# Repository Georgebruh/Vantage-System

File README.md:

# Vantage

Design files and firmware of the **Vantage** IoT sensor node, by Team sevenUP. The node is the field unit of a
flood-monitoring system. This repository holds the hardware (schematics, PCB layout, libraries, drawings and the
instruction documents) and the node firmware.

**Current revision: Rev A** (2026-10-25), tag `rev-A`.

| Board | Status |
|---|---|
| Sensor board | Schematic and PCB complete. Single-sided, made at home by toner transfer. |
| Power board | Schematic complete. PCB layout not started yet. |

The node is two boards joined by one 6-way JST XH cable (J1 to J1):

- **Sensor board**: carries the ESP32-S3 dev board (YD-ESP32-S3, header rows 25.4 mm apart) and the sensor
  interfaces: AJ-SR04M ultrasonic, BME280, rain gauge, TF-Luna (optional).
- **Power board**: 18650 cell with protection, solar MPPT charger, 3.3 V buck-boost with ideal diode, switched
  5 V for the sensors (SENS_EN) and two INA226 current monitors.

## Repository layout

```
Vantage-Hardware/
├── sensor-board/           KiCad project of the sensor board (schematic + PCB)
├── power-board/            KiCad project of the power board (schematic)
├── lib/                    shared Vantage symbol and footprint library
├── outputs/
│   ├── sensor-board/       schematic PDF, copper artwork, assembly drawing, BOM, drill table
│   └── power-board/        schematic PDF, BOM
├── docs/                   instruction documents (PDF)
│   └── src/                document sources, figures, fonts and build script
├── firmware/               ESP32-S3 firmware (PlatformIO) and the gateway receiver
└── tools/                  script that regenerates the drawings in outputs/
```

## Files

### KiCad design files

| File | Description |
|---|---|
| `sensor-board/Vantage_Sensor.kicad_pro` | Sensor board project (design rules for toner transfer: 0.6 / 1.0 mm tracks, 0.5 mm gaps) |
| `sensor-board/Vantage_Sensor.kicad_sch` | Sensor board schematic |
| `sensor-board/Vantage_Sensor.kicad_pcb` | Sensor board PCB, 110 × 30 mm, copper on the bottom only, two wire links on top |
| `sensor-board/fp-lib-table`, `sym-lib-table` | Project library tables, pointing to `lib/` |
| `power-board/Vantage_Power.kicad_pro` | Power board project (same toner-transfer design rules, ready for the layout) |
| `power-board/Vantage_Power.kicad_sch` | Power board schematic |
| `power-board/fp-lib-table`, `sym-lib-table` | Project library tables, pointing to `lib/` |

### Library

| File | Description |
|---|---|
| `lib/Vantage.kicad_sym` | Symbols: ESP32-S3 dev board, INA226 module, CN3791, BMS and DC-DC modules, LM66100, TPS2051B |
| `lib/Vantage.pretty/` | Footprints with enlarged pads for toner transfer and hand drilling; SMD footprints placed on the copper side |

### Drawings and tables (`outputs/`)

| File | Description |
|---|---|
| `outputs/sensor-board/Vantage_Sensor_Schematic.pdf` | Sensor board schematic |
| `outputs/sensor-board/Vantage_Sensor_Copper-Artwork_Letter.pdf` | Copper artwork, 1:1, four copies on US Letter. **Print at 100 % / Actual size, do not mirror.** |
| `outputs/sensor-board/Vantage_Sensor_Copper-Artwork_A4.pdf` | Same, on A4 |
| `outputs/sensor-board/Vantage_Sensor_Assembly-Drawing.pdf` | Assembly drawing, 2:1: component side and copper side |
| `outputs/sensor-board/Vantage_Sensor_BOM.csv` | Sensor board bill of materials |
| `outputs/sensor-board/Vantage_Sensor_Drill.csv` | Drill sizes and counts |
| `outputs/power-board/Vantage_Power_Schematic.pdf` | Power board schematic |
| `outputs/power-board/Vantage_Power_BOM.csv` | Power board bill of materials |

### Documents (`docs/`)

The documents follow the layout of ISO documents: cover, contents, foreword, introduction, numbered clauses
(scope, references, terms, ...), normative and informative annexes, bibliography.

| File | Description |
|---|---|
| `docs/VNT-001_Sensor-board_Fabrication-assembly-test.pdf` | **VNT-001** Vantage — Sensor board — Fabrication, assembly and test |
| `docs/VNT-002_Power-board_Description-and-test.pdf` | **VNT-002** Vantage — Power board — Description and test |
| `docs/src/VNT-001.md`, `VNT-002.md` | Document sources (edit these, then rebuild the PDFs) |
| `docs/src/build.py` | Builds the PDFs from the sources |
| `docs/src/iso.css` | Page layout and styles |
| `docs/src/figures/` | Figures used by the documents |
| `docs/src/fonts/` | Caladea font (SIL Open Font License, `OFL.txt`) |

### Firmware (`firmware/`)

| File | Description |
|---|---|
| `firmware/README.md` | Setup, build environments, power modes and the data format |
| `firmware/platformio.ini` | PlatformIO project: `field` (normal operation) and `bench` (bench and functional tests) |
| `firmware/include/config.h` | Node ID, gateway URL, mounting height, intervals and battery thresholds |
| `firmware/include/pins.h` | Pin map (VNT-001, Annex C) |
| `firmware/include/secrets.example.h` | Template for the Wi-Fi credentials; copy to `secrets.h`, which is not committed |
| `firmware/src/` | Firmware sources: sensors, rain gauge, power monitors, uplink, sleep and power modes |
| `firmware/tools/receiver.py` | Receiver for the gateway computer; writes the readings to a CSV file |

### Tools

| File | Description |
|---|---|
| `tools/make_outputs.py` | Regenerates the schematic PDFs, copper artwork, assembly drawing and document figures with `kicad-cli` |

## Opening the design

The KiCad files are in the KiCad 7 format; KiCad 8, 9 and 10 open them. The first save in KiCad 10 upgrades the
file format; commit that upgrade on its own, without other changes, so later diffs stay readable.

Both projects use the shared library in `lib/` through their own library tables, so no global library setup is
needed.

## Title blocks

Every file carries the same title block content: **Team sevenUP**, title **Vantage — Sensor board** or
**Vantage — Power board**, date and revision. No comment lines. The documents carry the same fields in the title
block on their cover.

## Revisions

All files of a release share one revision letter, shown in every title block and on the document covers. Each
release is tagged `rev-<letter>` and listed in [`CHANGELOG.md`](CHANGELOG.md). Things that need to change are
tracked as GitHub issues.

To make a new revision:

1. Change the design in KiCad.
2. Set the new revision letter and date in the title block of every changed file (Page Settings in KiCad).
3. Regenerate the drawings: `python3 tools/make_outputs.py`, or plot them from KiCad.
4. Update the BOM and drill CSV files if parts or holes changed.
5. Update the document sources (`edition`, `date`, `rev` and the content) and rebuild: `python3 docs/src/build.py`.
6. Add the revision to `CHANGELOG.md`, commit, and tag it `rev-<letter>`.

## Rebuilding the outputs

Drawings (needs KiCad's `kicad-cli` on the PATH, or its path in `KICAD_CLI`):

```
pip install pypdf reportlab
python3 tools/make_outputs.py
```

Documents:

```
pip install markdown beautifulsoup4 weasyprint
python3 docs/src/build.py
```

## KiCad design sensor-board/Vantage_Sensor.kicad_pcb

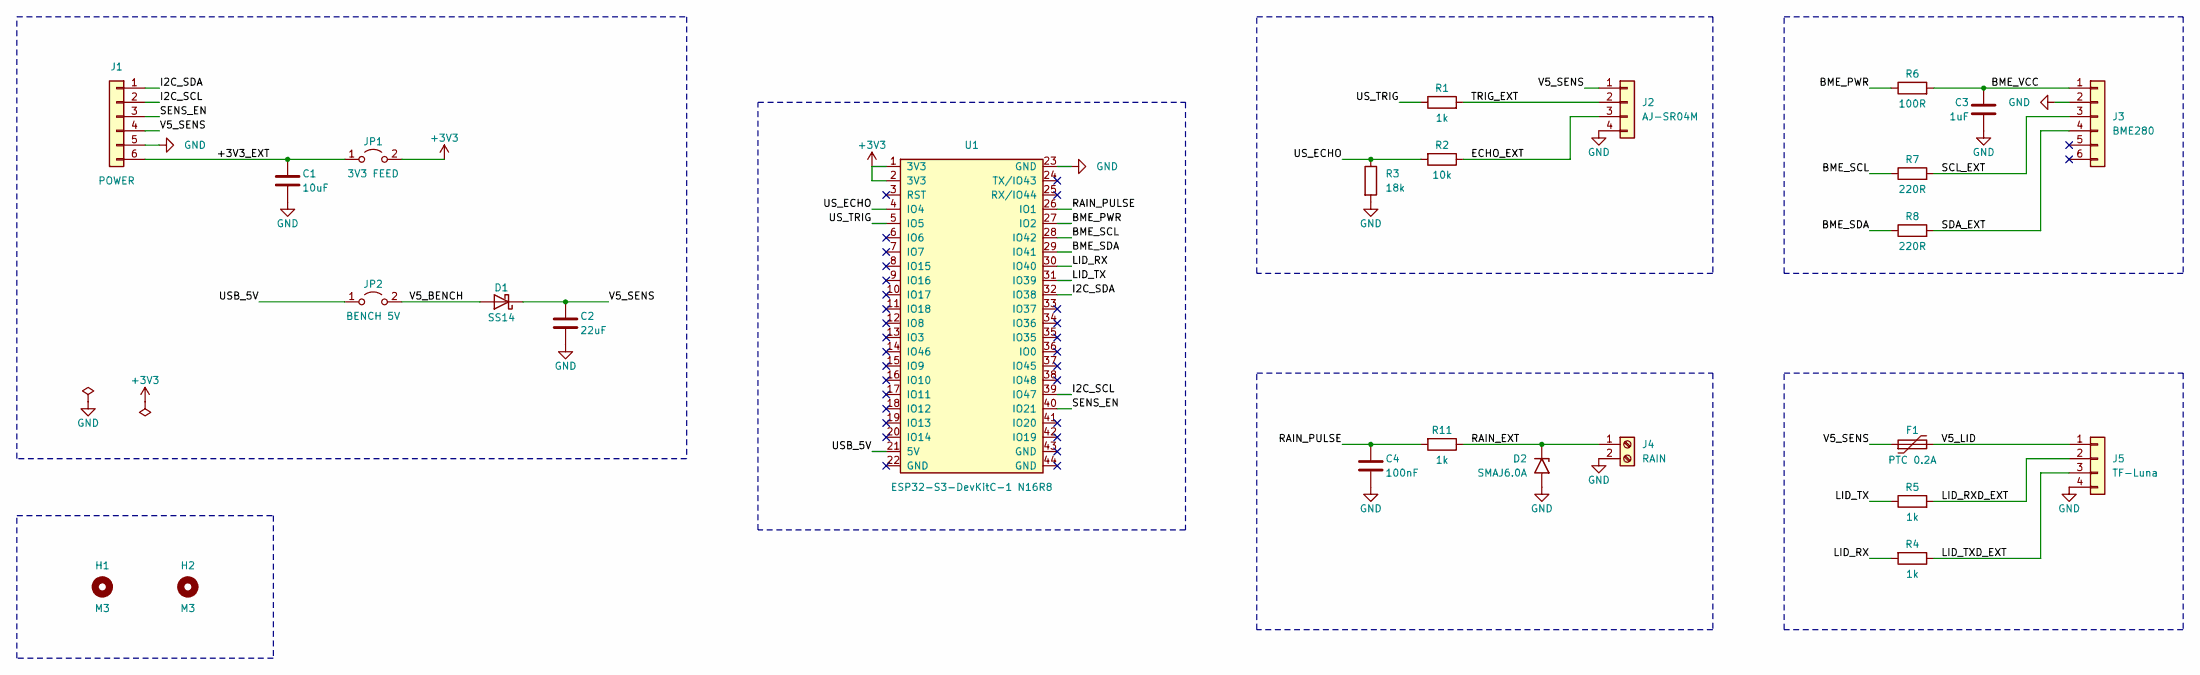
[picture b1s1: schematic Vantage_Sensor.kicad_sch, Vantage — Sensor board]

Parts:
C1: 10uF; C_1206_HandSolder_Bottom
C2: 22uF; C_1206_HandSolder_Bottom
C3: 1uF; C_1206_HandSolder_Bottom
C4: 100nF; C_1206_HandSolder_Bottom
D1: SS14; D_SMA_HandSolder_Bottom
D2: SMAJ6.0A; D_SMA_HandSolder_Bottom
F1: PTC 0.2A; Fuse_1812_HandSolder_Bottom
H1, H2: M3; MountingHole_3.2mm_M3_KeepCopper3.5mm
J1: POWER; JST_XH_S6B-XH-A_1x06_P2.50mm_Horizontal_Toner
J2: AJ-SR04M; AJ-SR04M_Socket_1x04_Upright
J3: BME280; PinSocket_1x06_P2.54mm_Vertical_Toner
J4: RAIN; TerminalBlock_3.5mm_1x02_Toner
J5: TF-Luna; PinHeader_1x04_P2.54mm_Vertical_Toner
JP1: 3V3 FEED; PinHeader_1x02_P2.54mm_Vertical_Toner
JP2: BENCH 5V; PinHeader_1x02_P2.54mm_Vertical_Toner
R1, R4, R5, R11: 1k; R_1206_HandSolder_Bottom
R2: 10k; R_1206_HandSolder_Bottom
R3: 18k; R_1206_HandSolder_Bottom
R6: 100R; R_1206_HandSolder_Bottom
R7, R8: 220R; R_1206_HandSolder_Bottom
U1: ESP32-S3-DevKitC-1 N16R8; ESP32-S3-DevKitC-1_Socket_Row25.40mm

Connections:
+3V3: JP1.2 (B), U1.1 (3V3), U1.2 (3V3)
/+3V3_EXT: C1.1, J1.6, JP1.1 (A)
/BME_PWR: R6.1, U1.27 (IO2)
/BME_SCL: R7.1, U1.28 (IO42)
/BME_SDA: R8.1, U1.29 (IO41)
/BME_VCC: C3.1, J3.1, R6.2
/ECHO_EXT: J2.3, R2.1
/I2C_SCL: J1.2, U1.39 (IO47)
/I2C_SDA: J1.1, U1.32 (IO38)
/LID_RX: R4.2, U1.30 (IO40)
/LID_RXD_EXT: J5.2, R5.2
/LID_TX: R5.1, U1.31 (IO39)
/LID_TXD_EXT: J5.3, R4.1
/RAIN_EXT: D2.1 (A1), J4.1, R11.1
/RAIN_PULSE: C4.1, R11.2, U1.26 (IO1)
/SCL_EXT: J3.3, R7.2
/SDA_EXT: J3.4, R8.2
/SENS_EN: J1.3, U1.40 (IO21)
/TRIG_EXT: J2.2, R1.2
/USB_5V: JP2.1 (A), U1.21 (5V)
/US_ECHO: R2.2, R3.1, U1.4 (IO4)
/US_TRIG: R1.1, U1.5 (IO5)
/V5_BENCH: D1.2 (A), JP2.2 (B)
/V5_LID: F1.2, J5.1
/V5_SENS: C2.1, D1.1 (K), F1.1, J1.4, J2.1
GND: C1.2, C2.2, C3.2, C4.2, D2.2 (A2), J1.5, J2.4, J3.2, J4.2, J5.4, R3.2, U1.23 (GND)

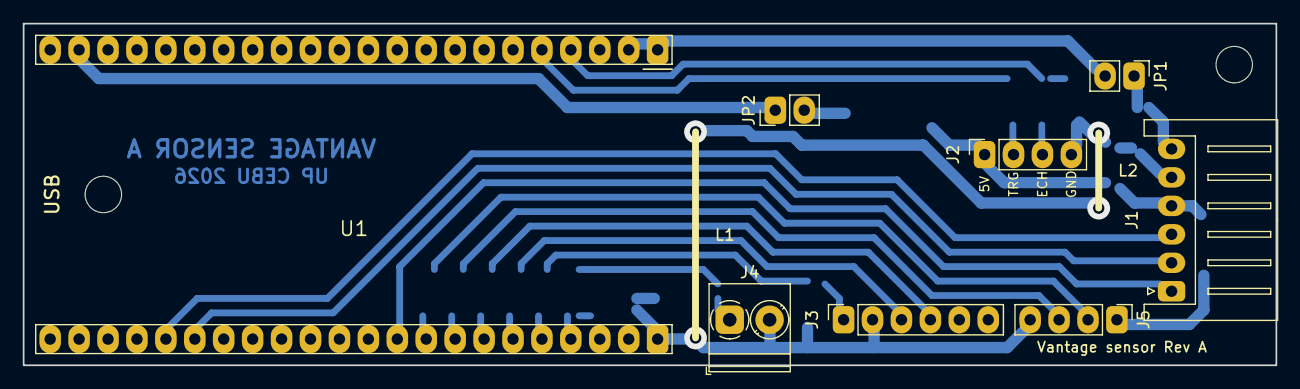
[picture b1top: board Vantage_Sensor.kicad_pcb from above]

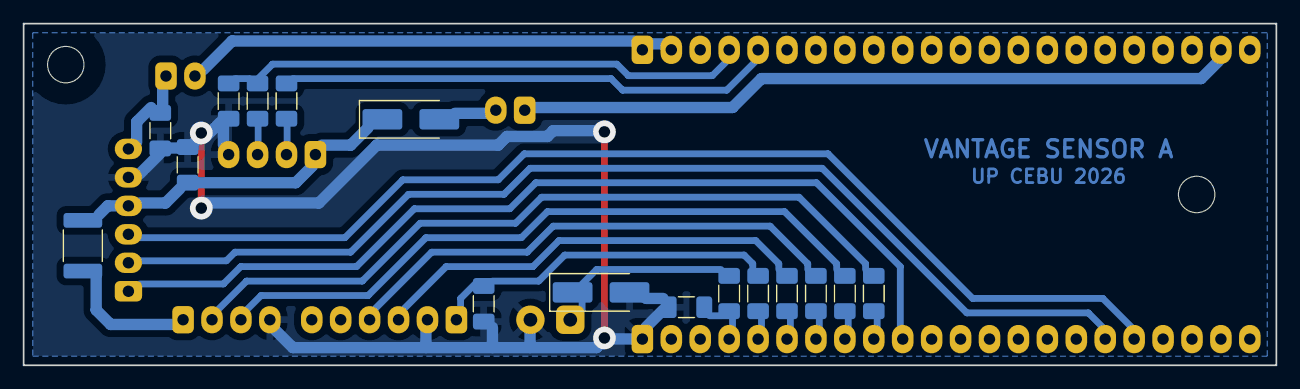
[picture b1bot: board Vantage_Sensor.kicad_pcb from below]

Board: 2 copper layers, 110.0 x 30.0 mm, 26 parts (16 on the bottom side), 26 nets.

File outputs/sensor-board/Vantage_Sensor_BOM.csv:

Item,Qty,References,Value,Package,Mounted on
1,1,C1,10uF,"1206 (3216), X7R/X5R, >=10 V",copper side (SMD)
2,1,C2,22uF,"1206 (3216), X7R/X5R, >=10 V",copper side (SMD)
3,1,C3,1uF,"1206 (3216), X7R/X5R, >=10 V",copper side (SMD)
4,1,C4,100nF,"1206 (3216), X7R/X5R, >=10 V",copper side (SMD)
5,1,D1,SS14,SMA (DO-214AC),copper side (SMD)
6,1,D2,SMAJ6.0A,SMA (DO-214AC),copper side (SMD)
7,1,F1,PTC 0.2A,1812 (4532),copper side (SMD)
8,2,H1 H2,M3,M3 screw + standoff (no part on the PCB),-
9,1,J1,POWER,"JST S6B-XH-A (XH 6-pin, side entry)",component side (THT)
10,1,J2,AJ-SR04M,1x4 female header 2.54 mm,component side (THT)
11,1,J3,BME280,1x6 female header 2.54 mm,component side (THT)
12,1,J4,RAIN,"2-way screw terminal, 3.5 mm pitch",component side (THT)
13,1,J5,TF-Luna,1x4 male header 2.54 mm,component side (THT)
14,1,JP1,3V3 FEED,1x2 male header 2.54 mm + jumper cap,component side (THT)
15,1,JP2,BENCH 5V,1x2 male header 2.54 mm + jumper cap,component side (THT)
16,4,R1 R4 R5 R11,1k,1206 (3216),copper side (SMD)
17,1,R2,10k,1206 (3216),copper side (SMD)
18,1,R3,18k,1206 (3216),copper side (SMD)
19,1,R6,100R,1206 (3216),copper side (SMD)
20,2,R7 R8,220R,1206 (3216),copper side (SMD)
21,1,U1,ESP32-S3-DevKitC-1 N16R8,"2x 1x22 female header 2.54 mm, rows 25.4 mm apart",component side (THT)

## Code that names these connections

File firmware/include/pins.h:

#pragma once

// VNT-001 Annex C, Table C.5
constexpr int PIN_RAIN = 1;
constexpr int PIN_BME_PWR = 2;
constexpr int PIN_US_ECHO = 4;
constexpr int PIN_US_TRIG = 5;
constexpr int PIN_SENS_EN = 21;
constexpr int PIN_PWR_SDA = 38;
constexpr int PIN_LID_TX = 39;
constexpr int PIN_LID_RX = 40;
constexpr int PIN_BME_SDA = 41;
constexpr int PIN_BME_SCL = 42;
constexpr int PIN_PWR_SCL = 47;

constexpr uint8_t INA_SOLAR_ADDR = 0x40;
constexpr uint8_t INA_BATT_ADDR = 0x44;
